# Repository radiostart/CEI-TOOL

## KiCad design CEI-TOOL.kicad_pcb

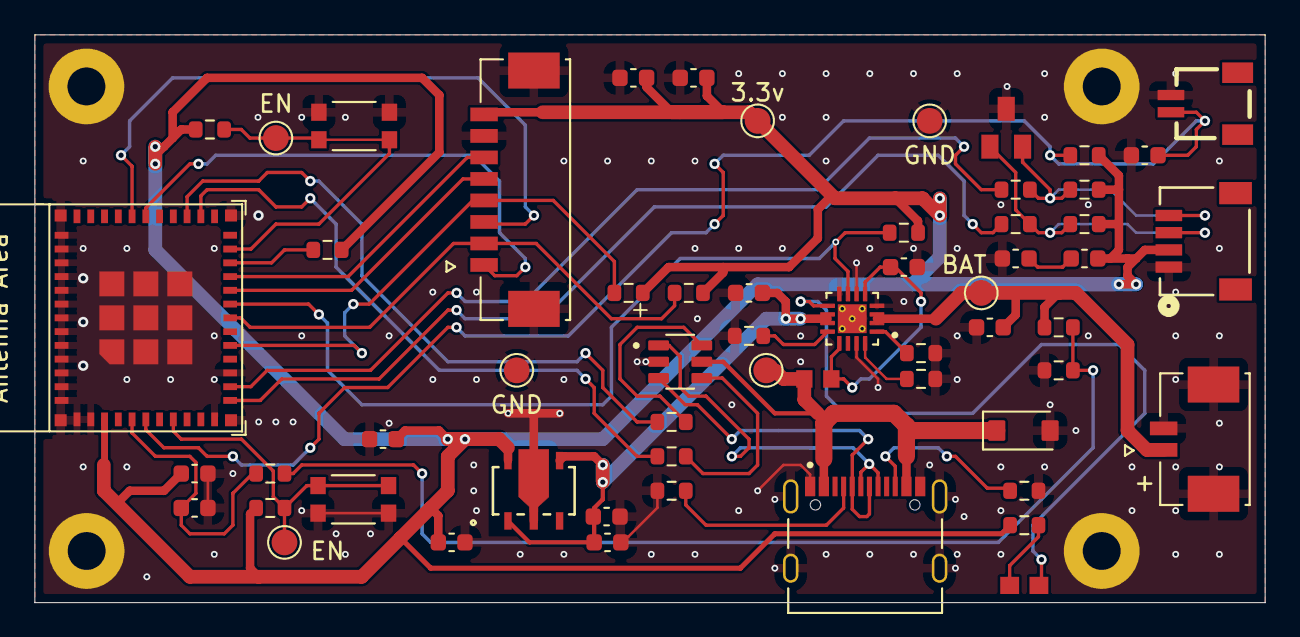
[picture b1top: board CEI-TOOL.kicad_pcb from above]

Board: 2 copper layers, 71.5 x 33.0 mm, 61 parts (0 on the bottom side), 37 nets.

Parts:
3.3v: TestPoint_Pad_D1.5mm
BAT: TestPoint_Pad_D1.5mm
C1, C2, C3, C4, C5, C6, C10: 10µF; C_0603_1608Metric
C7, C12: 0.1µF; C_0603_1608Metric
C8, C13: 1µF; C_0603_1608Metric
C9: 0.01µF; C_0603_1608Metric
C11: 0.47µF; C_0603_1608Metric
C14: 22µF; C_0603_1608Metric
D2: PESD5V0S2BT; SOT23
D3: LTST-S270KRKT; 0603
D4: SMF5.0A; P37_SOD-123FL
EN: TestPoint_Pad_D1.5mm
EN#2: TestPoint_Pad_D1.5mm
F1: 0603L100SLYR; FUSC1608X100N
GND: TestPoint_Pad_D1.5mm
GND#2: TestPoint_Pad_D1.5mm
H1, H2, H3, H4: MountingHole_Pad; MountingHole_2.2mm_M2_Pad
J1: TYPE-C-31-M-12; HRO_TYPE-C-31-M-12
J2: 532610871; MOLEX_532610871
J4: SM04B-SRSS-TB; CONN_SM04B-SRSS-TB_JST
J5: 532610271; MOLEX_532610271
J6: SM02B-SRSS-TB_LF__SN_
R1, R2, R16, R17, R20: 47kΩ; R_0603_1608Metric
R3, R9, R11, R13, R22: 10kΩ; R_0603_1608Metric
R4, R6: 5.1kΩ; R_0603_1608Metric
R5: 1.8kΩ; R_0603_1608Metric
R7: 3.3kΩ; R_0603_1608Metric
R8, R10, R21: 2.2kΩ; R_0603_1608Metric
R12, R14, R18, R19: 22Ω; R_0603_1608Metric
R15: 1kΩ; R_0603_1608Metric
S1, S3: KMR211NGLFS; SW_KMR211NGLFS
U1: ESP32-C3-MINI-1
U2: XC6220B331PR-G; SOT-89-5_TOR
U3: BQ24075RGTT; QFN50P300X300X100-17N
U4: USBLC6-2SC6; SOT95P280X145-6N

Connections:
+3.3V: 3.3v.1, C5.1, C6.2, C8.1, C10.1, C12.1, C13.2, J2.8, J4.2, R8.1, R9.1, R10.2, R11.1, R13.1, R16.2, R17.2, R20.1, R21.1, R22.2, U1.3 (3V3), U2.5 (VOUT)
BAT: BAT.1, C2.1, J5.1, R2.1, U3.2 (BAT), U3.3 (BAT)
BOOT_BTN: EN.1, R13.2, S3.1, S3.2, U1.23 (GPIO9)
EN_BTN: EN#2.1, R9.2, S1.1, S1.2, U1.8 (EN/CHIP_PU)
GND: C1.2, C2.2, C3.2, C4.2, C5.2, C6.1, C7.1, C8.2, C9.2, C10.2, C11.2, C12.2, C14.2, D2.3, D4.2 (A), GND.1, GND#2.1, H1.1, H2.1, H3.1, H4.1, J1.A1_B12 (GND), J1.B1_A12 (GND), J1.S1 (SHIELD), J1.S2 (SHIELD), J1.S3 (SHIELD), J1.S4 (SHIELD), J2.7, J2.S1 (SHIELD1), J2.S2 (SHIELD2), J4.1, J5.2, J5.S1 (SHIELD1), J5.S2 (SHIELD2), J6.2, R1.2, R3.2, R4.2, R5.2, R6.2, R7.2, S1.3, S1.4, S3.3, S3.4, U1.1 (GND), U1.2 (GND), U1.11 (GND), U1.14 (GND), U1.36 (GND), U1.37 (GND), U1.38 (GND), U1.39 (GND), U1.40 (GND), U1.41 (GND), U1.42 (GND), U1.43 (GND), U1.44 (GND), U1.45 (GND), U1.46 (GND), U1.47 (GND), U1.48 (GND), U1.49 (GND), U1.50 (GND), U1.51 (GND), U1.52 (GND), U1.53 (GND), U2.2 (VSS), U3.4 (~CE), U3.6 (EN1), U3.8 (VSS), U3.15 (SYSOFF), U3.17 (EP), U4.2
I2C_SCL: R19.2, U1.13 (GPIO1/ADC1_CH1/XTAL_32K_N)
I2C_SDA: R18.1, U1.12 (GPIO0/ADC1_CH0/XTAL_32K_P)
MAIN_BTN: C9.1, J6.1, R11.2, U1.6 (GPIO3/ADC1_CH3)
MCU-(GPIO2): C11.1, R15.2, U1.5 (GPIO2/ADC1_CH2)
unnamed: C7.2, C13.1
unnamed: D2.1, J4.3, R10.1, R18.2
unnamed: D2.2, J4.4, R8.2, R19.1
unnamed: D3.2, R21.2
unnamed: J1.A5 (CC1), R4.1
unnamed: J1.B5 (CC2), R6.1
unnamed: J1.A7 (DN1), J1.B7 (DN2), U4.3
unnamed: J1.A6 (DP1), J1.B6 (DP2), U4.1
unnamed: R1.1, R2.2, R15.1
unnamed: R12.2, U4.6
unnamed: R14.2, U4.4
unnamed: R22.1, U1.22 (GPIO8)
unnamed: C1.1, F1.1, U3.5 (EN2), U3.13 (IN)
unnamed: R7.1, U3.12 (ILIM)
unnamed: R5.1, U3.16 (ISET)
unnamed: R3.1, U3.1 (TS)
unnamed: D3.1, U3.9 (~CHG)
SPI_BUSY: J2.1, U1.30 (GPIO20/U0RXD)
SPI_CLK: J2.5, U1.20 (GPIO6)
SPI_CS: J2.4, R16.1, U1.16 (GPIO10)
SPI_DC: J2.3, U1.31 (GPIO21/U0TXD)
SPI_MOSI(DIN): J2.6, U1.21 (GPIO7)
SPI_RST: J2.2, R17.1, U1.18 (GPIO4/ADC1_CH4)
TP-VBUS: D4.1 (C), F1.2, J1.A4_B9 (VBUS), J1.B4_A9 (VBUS), U4.5
USB_D+: R12.1, U1.27 (GPIO19/USB_D+)
USB_D-: R14.1, U1.26 (GPIO18/USB_D-)
USB_PGOOD: R20.2, U1.19 (GPIO5/ADC2_CH0), U3.7 (~PGOOD)
VSYS: C3.1, C4.1, C14.1, U2.1 (CE), U2.4 (VIN), U3.10 (OUT), U3.11 (OUT)

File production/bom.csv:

Designator,Footprint,Quantity,Value,LCSC Part #
"C1, C10, C2, C3, C4, C5, C6",0603,7,10µF,
C11,0603,1,0.47µF,
"C12, C7",0603,2,0.1µF,
"C13, C8",0603,2,1µF,
C14,0603,1,22µF,
C9,0603,1,0.01µF,
D2,SOT23,1,PESD5V0S2BT,
D3,0603,1,LTST-S270KRKT,
D4,P37_SOD-123FL,1,SMF5.0A,
F1,FUSC1608X100N,1,0603L100SLYR,
J1,HRO_TYPE-C-31-M-12,1,TYPE-C-31-M-12,
J2,MOLEX_532610871,1,532610871,
J4,CONN_SM04B-SRSS-TB_JST,1,SM04B-SRSS-TB,
J5,MOLEX_532610271,1,532610271,
J6,SM02B-SRSS-TB_LF__SN_,1,SM02B-SRSS-TB_LF__SN_,
"R1, R16, R17, R2, R20",0603,5,47kΩ,
"R10, R21, R8",0603,3,2.2kΩ,
"R11, R13, R22, R3, R9",0603,5,10kΩ,
"R12, R14, R18, R19",0603,4,22Ω,
R15,0603,1,1kΩ,
"R4, R6",0603,2,5.1kΩ,
R5,0603,1,1.8kΩ,
R7,0603,1,3.3kΩ,
"S1, S3",SW_KMR211NGLFS,2,KMR211NGLFS,
U1,ESP32-C3-MINI-1,1,ESP32-C3-MINI-1,
U2,SOT-89-5_TOR,1,XC6220B331PR-G,
U3,QFN50P300X300X100-17N,1,BQ24075RGTT,
U4,SOT95P280X145-6N,1,USBLC6-2SC6,

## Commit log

2026-03-06 edit
2026-03-16 회소 수정

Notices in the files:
parts and their libraries:
COPYRIGHT: Copyright (C) 2022 Ultra Librarian. All rights reserved.
COPYRIGHT: Copyright (C) 2024 Ultra Librarian. All rights reserved.
